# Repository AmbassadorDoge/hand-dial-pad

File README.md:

# hand-dial-pad

I honestly couldn't decide on a better name than this... 

Anyways, here's a rundown of this hackpad. I play Minecraft without sprint lock, so the design kinda mimics what my hand is used to. Its functions are mainly responding to stuff and controlling devices. I will probably find a better use for the LEDs, but for right now, they are on the device for fun. 

## Schematic

## PCB

## CAD + View

## BOM
4x switches, 4x caps, 2x encoders, 4x leds, 1x XIAO RP2040, 1x 3DP case

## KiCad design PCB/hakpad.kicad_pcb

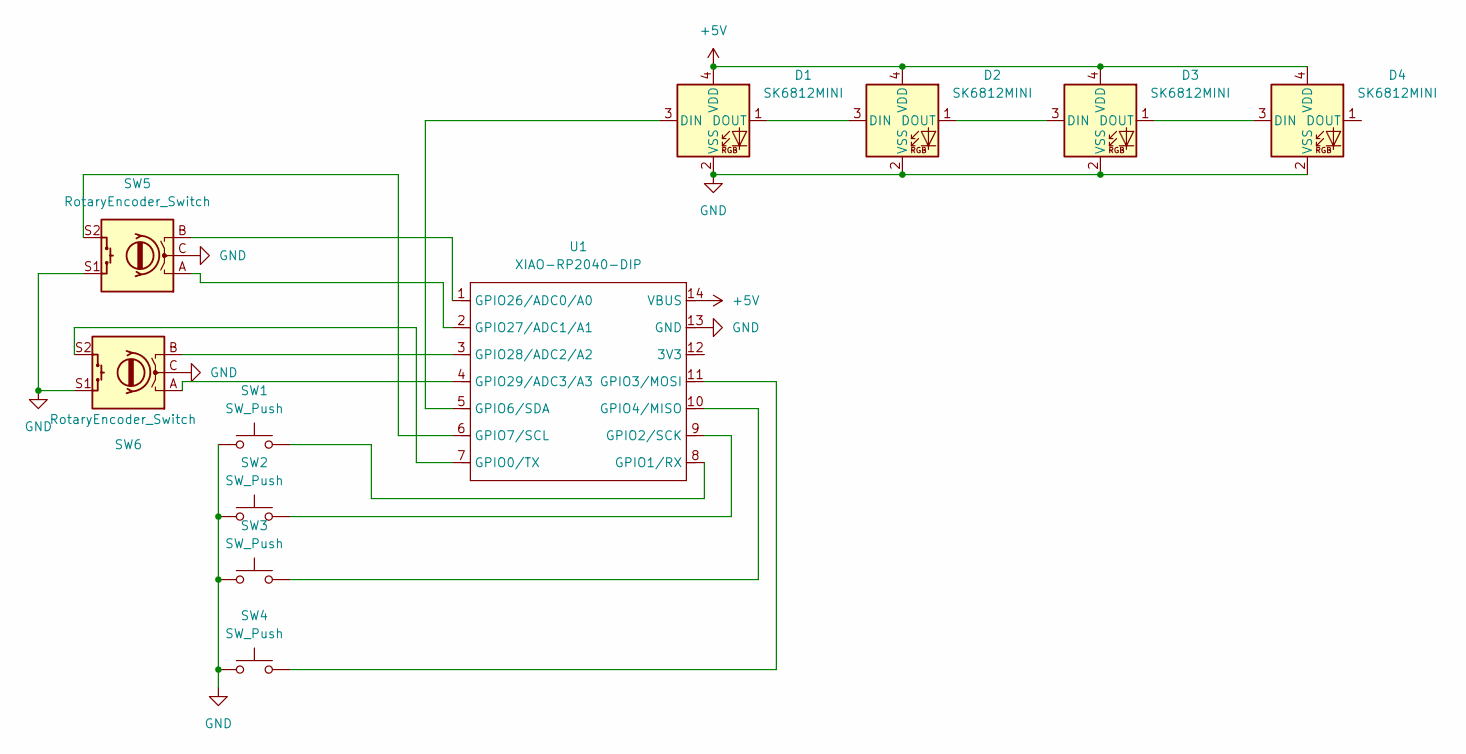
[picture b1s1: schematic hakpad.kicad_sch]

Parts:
D1, D2, D3, D4: SK6812MINI; LED_SK6812MINI_PLCC4_3.5x3.5mm_P1.75mm
SW1, SW2, SW3, SW4: SW_Push; SW_Cherry_MX_1.00u_PCB
SW5, SW6: RotaryEncoder_Switch; RotaryEncoder_Alps_EC11E-Switch_Vertical_H20mm
U1: XIAO-RP2040-DIP; XIAO-RP2040-SMD

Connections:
+5V: D1.4 (VDD), D2.4 (VDD), D3.4 (VDD), D4.4 (VDD), U1.14 (VBUS)
GND: D1.2 (VSS), D2.2 (VSS), D3.2 (VSS), D4.2 (VSS), SW1.1, SW2.1, SW3.1, SW4.1, SW5.C, SW5.S1, SW6.C, SW6.S1, U1.13 (GND)
unnamed: D1.3 (DIN), U1.5 (GPIO6/SDA)
unnamed: D1.1 (DOUT), D2.3 (DIN)
unnamed: D2.1 (DOUT), D3.3 (DIN)
unnamed: D3.1 (DOUT), D4.3 (DIN)
unnamed: SW6.S2, U1.7 (GPIO0/TX)
unnamed: SW1.2, U1.8 (GPIO1/RX)
unnamed: SW2.2, U1.9 (GPIO2/SCK)
unnamed: SW4.2, U1.11 (GPIO3/MOSI)
unnamed: SW3.2, U1.10 (GPIO4/MISO)
unnamed: SW5.S2, U1.6 (GPIO7/SCL)
unnamed: SW5.B, U1.1 (GPIO26/ADC0/A0)
unnamed: SW5.A, U1.2 (GPIO27/ADC1/A1)
unnamed: SW6.B, U1.3 (GPIO28/ADC2/A2)
unnamed: SW6.A, U1.4 (GPIO29/ADC3/A3)

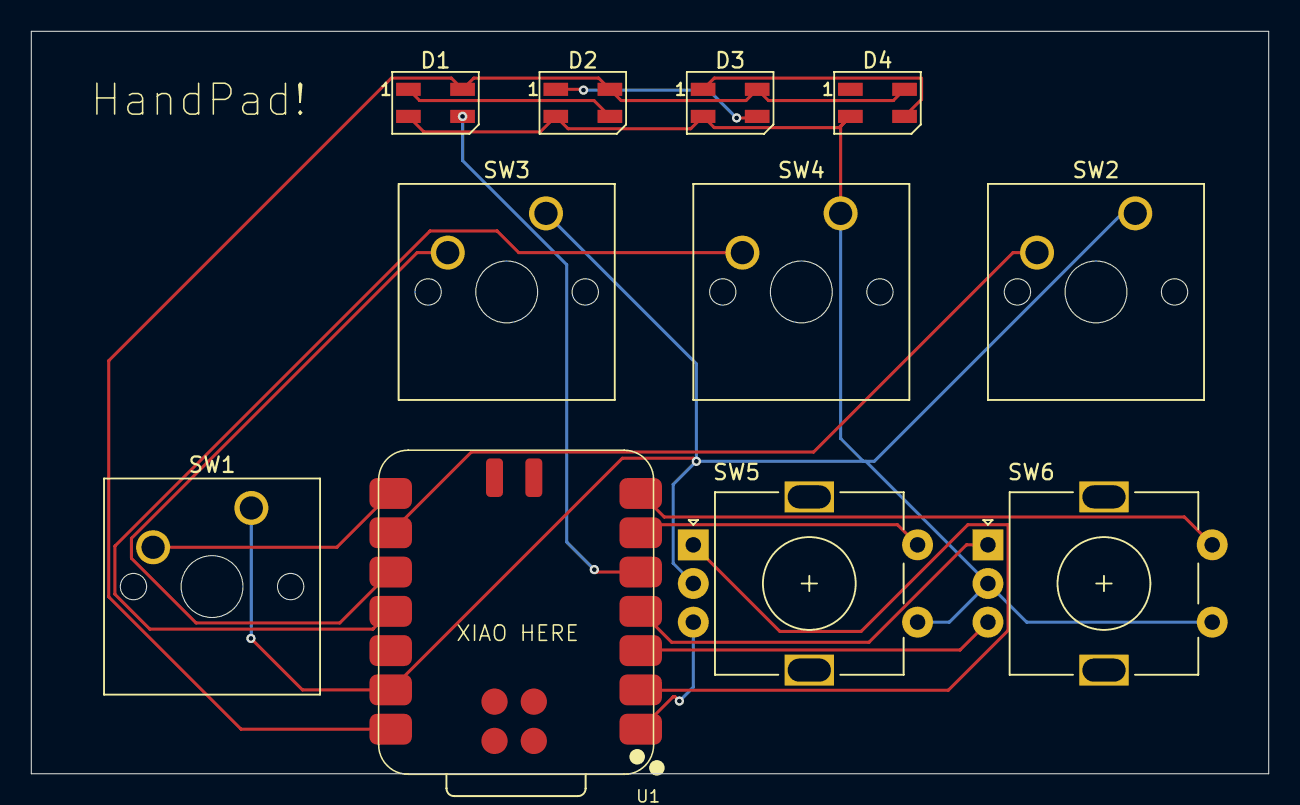
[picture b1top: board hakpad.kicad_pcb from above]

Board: 2 copper layers, 80.0 x 48.0 mm, 11 parts (0 on the bottom side), 16 nets.

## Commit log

2025-06-20 Adding everything
2025-06-20 Update README.md
    forgot BOM
